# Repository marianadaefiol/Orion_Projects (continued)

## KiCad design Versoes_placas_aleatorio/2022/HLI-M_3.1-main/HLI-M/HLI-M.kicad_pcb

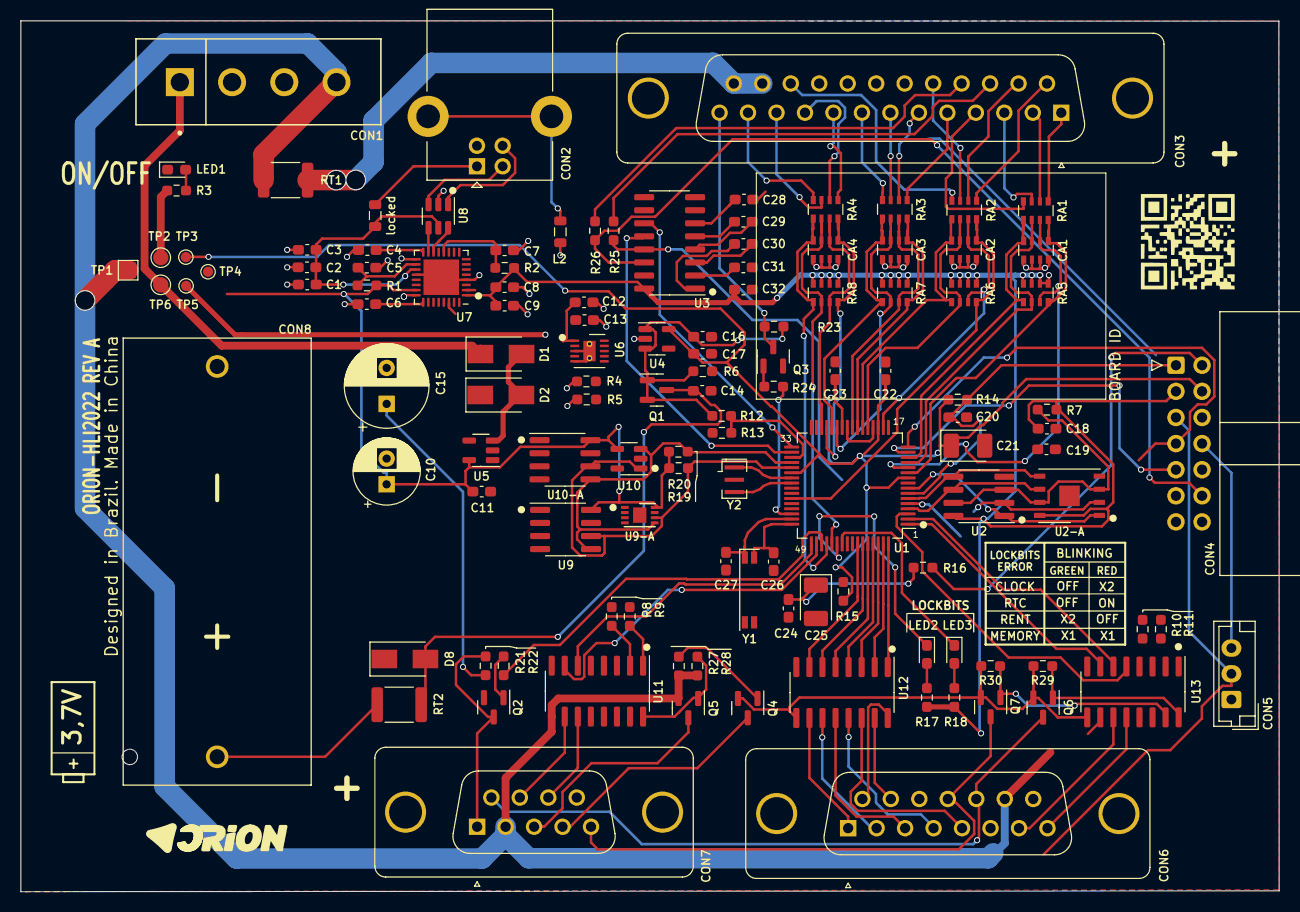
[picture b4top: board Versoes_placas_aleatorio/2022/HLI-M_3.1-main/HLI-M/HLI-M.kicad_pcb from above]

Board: 2 copper layers, 122.4 x 84.7 mm, 124 parts (0 on the bottom side), 132 nets.

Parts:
C1, C3, C5, C7, C9, C11, C14, C16, C17, C18, C22, C23, C24, C28, C29, C30, C31, C32: 100nF; C_0603_1608Metric_Pad1.08x0.95mm_HandSolder
C2, C8: 4,7uF; C_0603_1608Metric_Pad1.08x0.95mm_HandSolder
C4, C12, C13: 1uF; C_0603_1608Metric_Pad1.08x0.95mm_HandSolder
C6: 2,2nF; C_0603_1608Metric_Pad1.08x0.95mm_HandSolder
C10: 220uFx16V; CP_Radial_D6.3mm_P2.50mm
C15: 470uFx16v; CP_Radial_D8.0mm_P3.50mm
C19: 47pF; C_0603_1608Metric_Pad1.08x0.95mm_HandSolder
C20: 1nF; C_0603_1608Metric_Pad1.08x0.95mm_HandSolder
C21: 10UfX6V-Tan; CP_EIA-3528-12_Kemet-T_Pad1.50x2.35mm_HandSolder
C25: 10uFx6V-Tan; CP_EIA-3528-12_Kemet-T_Pad1.50x2.35mm_HandSolder
C26, C27: 12pF; C_0603_1608Metric_Pad1.08x0.95mm_HandSolder
CA1: 100nF; R_Array_Convex_4x0603
CA2, CA3, CA4: Array_Cap; R_Array_Convex_4x0603
CON1: Molex-0015244449-0
CON2: USB_B; USB_B_Lumberg_2411_02_Horizontal
CON3: DSUB-25_Male_Vertical_P2.77x2.84mm_MountingHoles
CON4: Connector_Adapter; IDC-Header_2x07_P2.54mm_Horizontal
CON5: Connector_Audio; JST_EH_B3B-EH-A_1x03_P2.50mm_Vertical
CON6: Conn_01x15; DSUB-15_Female_Vertical_P2.77x2.84mm_MountingHoles
CON7: Conn_01x09; DSUB-9_Female_Vertical_P2.77x2.84mm_MountingHoles
CON8: CR123A; BAT_BH123A
D1, D2: SSA33L; D_SMA
D8: SD1-13F; D_SMA
G1: LOGO
L2: BLM21PG221SN1D; L_0805_2012Metric
LED1: BLUE; LED_0603_1608Metric_Pad1.05x0.95mm_HandSolder
LED2: RED; LED_0603_1608Metric_Pad1.05x0.95mm_HandSolder
LED3: GREEN; LED_0603_1608Metric_Pad1.05x0.95mm_HandSolder
Q1: IRLML5103; SOT-23
Q2, Q3: BC817; SOT-23
Q4, Q5, Q6, Q7: BSS84; SOT-23
R1, R2: 2,2K; R_0603_1608Metric_Pad0.98x0.95mm_HandSolder
R3, R17, R18: 470R; R_0603_1608Metric_Pad0.98x0.95mm_HandSolder
R4, R5, R6: 10k; R_0603_1608Metric_Pad0.98x0.95mm_HandSolder
R7, R14: 22k; R_0603_1608Metric_Pad0.98x0.95mm_HandSolder
R8, R9, R10, R11, R16, R19, R20, R21, R23, R27, R28, R29, R30: 1K; R_0603_1608Metric_Pad0.98x0.95mm_HandSolder
R12: 1K5; R_0603_1608Metric_Pad0.98x0.95mm_HandSolder
R13: 3K3; R_0603_1608Metric_Pad0.98x0.95mm_HandSolder
R15, R22, R24: 22K; R_0603_1608Metric_Pad0.98x0.95mm_HandSolder
R25, R26: 33R; R_0603_1608Metric_Pad0.98x0.95mm_HandSolder
RA1: 1K; R_Array_Convex_4x0603
RA2, RA3, RA4, RA6, RA7, RA8: R_Pack04; R_Array_Convex_4x0603
RA5: 10K; R_Array_Convex_4x0603
RT1: 1,5A - 153F; R_1812_4532Metric
RT2: 300mA - 304N; R_1812_4532Metric
TP1: TestPoint; TestPoint_Pad_1.5x1.5mm
TP2, TP6: TestPoint; TestPoint_Pad_D1.5mm
TP3, TP4, TP5: TestPoint; TestPoint_Pad_D1.0mm
U1: PIC24HJ64GP206-I_PT; TQFP-64_10x10mm_P0.5mm
U2, U9, U10-A: SOIC-8_3.9x4.9mm_P1.27mm
U2-A: DFN-8-1EP_6x5mm_P1.27mm_EP2x2mm
U3: MAX3232; SOIC-16_3.9x9.9mm_P1.27mm
U4, U5: TPS7A0533PDBV; SOT-23-5
U6: VSON-10-1EP_3x3mm_P0.5mm_EP1.2x2mm_ThermalVias
U7: CY7C65215-32LTXI; QFN-32-1EP_5x5mm_P0.5mm_EP3.45x3.45mm
U8: USBLC6-2SC6; SOT-23-6
U9-A: DFN-8-1EP_3x2mm_P0.5mm_EP1.3x1.5mm
U10: 24AA02-OT; SOT-23-5
U11, U12, U13: ULN2003; SOIC-16_3.9x9.9mm_P1.27mm
Y1: Crystal_32KHz; Crystal_SMD_SeikoEpson_MC146-4Pin_6.7x1.5mm
Y2: Crystal_20MHz; Resonator_SMD_Murata_CSTxExxV-3Pin_3.0x1.1mm
locked: BLM21PG221SN1D; L_0805_2012Metric

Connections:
0: C1.2, C2.2, C3.2, C4.2, C5.2, C6.2, C7.2, C8.2, C9.2, C10.2, C11.2, C12.2, C13.2, C14.2, C15.2, C16.2, C17.2, C18.2, C19.2, C20.2, C21.2, C22.2, C23.2, C24.2, C25.2, C26.2, C27.2, C28.2, C31.2, C32.2, CA1.5, CA1.6, CA1.7, CA1.8, CA2.5, CA2.6, CA2.7, CA2.8, CA3.5, CA3.6, CA3.7, CA3.8, CA4.5, CA4.6, CA4.7, CA4.8, CON1.2, CON1.3, CON2.4 (GND), CON3.20, CON3.21, CON3.22, CON6.15, CON7.9, CON8.N, D8.1 (K), L2.1, LED1.1 (K), Q2.2 (E), Q3.2 (E), R4.1, R5.2, R6.2, R13.1, U1.9 (VSS), U1.20 (AVSS), U1.25 (VSS), U1.41 (VSS), U2.4 (VSS), U2-A.4, U3.15 (GND), U4.2 (GND), U5.2 (GND), U6.3 (GND), U6.5 (EN_B), U6.11 (DAP), U7.4 (VSSD), U7.17 (VSSD), U7.20 (VSSD), U7.24 (VSSA), U8.2 (GND), U9.4 (GND), U9-A.4, U10.2 (GND), U10-A.4, U11.8 (GND), U12.8 (GND), U13.8 (GND), Y1.2, Y2.2
+2V5: CON4.2, R16.1
+3.3VP: C17.1, C21.1, C22.1, C23.1, CON4.4, R14.1, R15.1, TP3.1, U1.10 (VDD), U1.19 (AVDD), U1.26 (VDD), U1.38 (VDD), U4.5 (OUT)
+5V: C12.1, CON1.1, CON3.19, CON4.6, CON5.1, D1.1 (K), TP6.1, U6.1 (CHG_IN)
+5VD: C15.1, C16.1, D1.2 (A), D2.2 (A), Q1.1 (G), Q1.2 (S), R3.1, R6.1, R12.2, R21.1, R23.1, TP2.1, U4.1 (IN), U4.3 (EN), U5.1 (IN), U5.3 (EN)
+12V: CON1.4, CON4.8, CON5.3, CON6.14, CON7.2, Q4.2 (S), Q5.2 (S), Q6.2 (S), Q7.2 (S), R27.1, R28.1, R29.1, R30.1, RT1.2, TP1.1, U11.9 (COM), U12.9 (COM), U13.9 (COM)
CIN: CON6.13, CON7.6, Q6.3 (D)
CIN1: CON7.3, Q5.3 (D)
COUT: CON6.12, CON7.5, Q7.3 (D)
COUT1: CON7.4, Q4.3 (D)
GND: CON4.5, CON5.2
INIB: CON3.13, Q3.3 (C), R23.2
K0: CA1.1, RA1.8 (R1.2), RA5.8 (R1.2), U1.11 (RB5)
K1: CA1.2, RA1.7 (R2.2), RA5.7 (R2.2), U1.12 (RB4)
K2: CA1.3, RA1.6 (R3.2), RA5.6 (R3.2), U1.13 (RB3)
K3: CA1.4, RA1.5 (R4.2), RA5.5 (R4.2), U1.14 (RB2)
K4: CA3.1, RA3.8 (R1.2), RA7.8 (R1.2), U1.23 (RB10)
K5: CA3.2, RA3.7 (R2.2), RA7.7 (R2.2), U1.24 (RB11)
K6: CA3.3, RA3.6 (R3.2), RA7.6 (R3.2), U1.27 (RB12)
K7: CA3.4, RA3.5 (R4.2), RA7.5 (R4.2), U1.28 (RB13)
K8: CA4.1, RA4.8 (R1.2), RA8.8 (R1.2), U1.29 (RB14)
K9: CA4.2, RA4.7 (R2.2), RA8.7 (R2.2), U1.30 (RB15)
KA: CA4.3, RA4.6 (R3.2), RA8.6 (R3.2), U1.53 (RD5)
KB: CA4.4, RA4.5 (R4.2), RA8.5 (R4.2), U1.52 (RD4)
KC: CA2.2, RA2.7 (R2.2), RA6.7 (R2.2), U1.18 (RB7)
KD: CA2.3, RA2.6 (R3.2), RA6.6 (R3.2), U1.21 (RB8)
KE: CA2.4, RA2.5 (R4.2), RA6.5 (R4.2), U1.22 (RB9)
K_0: CON3.1, RA1.1 (R1.1)
K_1: CON3.2, RA1.2 (R2.1)
K_2: CON3.3, RA1.3 (R3.1)
K_3: CON3.4, RA1.4 (R4.1)
K_4: CON3.5, RA3.1 (R1.1)
K_5: CON3.6, RA3.2 (R2.1)
K_6: CON3.7, RA3.3 (R3.1)
K_7: CON3.8, RA3.4 (R4.1)
K_8: CON3.9, RA4.1 (R1.1)
K_9: CON3.10, RA4.2 (R2.1)
K_A: CON3.11, RA4.3 (R3.1)
K_B: CON3.12, RA4.4 (R4.1)
K_C: CON3.15, RA2.2 (R2.1)
K_D: CON3.18, RA2.3 (R3.1)
K_E: CON3.23, RA2.4 (R4.1)
LED2: LED2.1 (K), U1.54 (RD6)
LED3: LED3.1 (K), U1.55 (RD7)
NOTE: CA2.1, RA2.8 (R1.2), RA6.8 (R1.2), U1.43 (RD9)
NOTE_: CON3.14, RA2.1 (R1.1)
unnamed: C1.1, C2.1, C3.1, D2.1 (K), U7.19 (VBUS), U8.5 (VBUS), locked.2
unnamed: C4.1, U7.16 (VCCD)
unnamed: C5.1, R1.2, U7.18 (~XRES)
unnamed: C6.1, U7.25 (GPIO_0)
unnamed: C7.1, R2.2, U7.12 (WAKEUP)
unnamed: U1.4 (SCK2/RG6), U2.6 (C), U2-A.6
unnamed: C24.1, C25.1, R16.2
unnamed: C26.1, U1.48 (RC14), Y1.3
unnamed: C27.1, Y1.1
unnamed: C28.1, U3.6 (VS-)
unnamed: C29.1, U3.4 (C2+)
unnamed: C29.2, U3.5 (C2-)
unnamed: C30.1, U3.1 (C1+)
unnamed: C30.2, U3.3 (C1-)
unnamed: C31.1, U3.2 (VS+)
unnamed: CON2.1 (VBUS), locked.1
unnamed: CON2.2 (D-), U8.3 (I/O2)
unnamed: CON2.3 (D+), U8.1 (I/O1)
unnamed: CON2.5 (Shield), L2.2
unnamed: CON3.16, R25.2
unnamed: CON3.17, R26.2
unnamed: CON3.24, CON3.25, RT1.1
unnamed: CON6.1, U12.10 (O7)
unnamed: CON6.2, U12.11 (O6)
unnamed: CON6.3, U12.12 (O5)
unnamed: CON6.4, U12.13 (O4)
unnamed: CON6.5, U12.14 (O3)
unnamed: CON6.6, U13.10 (O7)
unnamed: CON6.7, U13.11 (O6)
unnamed: CON6.8, U13.12 (O5)
unnamed: CON6.9, U12.16 (O1)
unnamed: CON6.10, U12.15 (O2)
unnamed: CON7.7, U11.10 (O7)
unnamed: CON7.8, U11.11 (O6)
unnamed: CON8.P, RT2.1
unnamed: LED1.2 (A), R3.2
unnamed: LED2.2 (A), R17.2
unnamed: LED3.2 (A), R18.2
unnamed: Q2.1 (B), R22.1
unnamed: Q3.1 (B), R24.1
unnamed: Q4.1 (G), R27.2, U11.15 (O2)
unnamed: Q5.1 (G), R28.2, U11.16 (O1)
unnamed: Q6.1 (G), R29.2, U13.16 (O1)
unnamed: Q7.1 (G), R30.2, U13.15 (O2)
unnamed: U2.3 (*W), U2.7 (*HOLD), U2-A.3, U2-A.7
unnamed: U1.5 (SDI2/RG7), U2.2 (Q), U2-A.2
unnamed: U1.6 (SDO2/RG8), U2.5 (D), U2-A.5
unnamed: U1.8 (*SS2/RG9), U2.1 (*S), U2-A.1
unnamed: U1.33 (U1TX/RF3), U3.11 (T1IN)
unnamed: U1.34 (U1RX/RF2), U3.12 (R1OUT)
unnamed: U1.39 (OSC1/CLKIN), Y2.1
unnamed: U1.40 (OSC2/CLKO), Y2.3
unnamed: C13.1, U6.4 (USB_SEL)
unnamed: U7.14 (USBDP), U8.6 (I/O1)
unnamed: U7.15 (USBDM), U8.4 (I/O2)
PGEC2: CON4.9, R11.1, U1.15 (RB1)
PGED2: CON4.7, R10.1, U1.16 (RB0)
PIN-CIN: R10.2, U13.2 (I2)
PIN-CIN1: R8.2, U11.2 (I2)
PIN-COUT: R11.2, U13.1 (I1)
PIN-COUT1: R9.2, U11.1 (I1)
PIN-INIB: R24.2, U1.46 (RD0)
PIN-PRINT: R22.2, U1.51 (RD3)
PIN-PWRMODE: R12.1, R13.2, U1.35 (RF6)
PIN-S0: U1.58 (RF0), U12.7 (I7)
PIN-S1: U1.59 (RF1), U12.6 (I6)
PIN-S2: U1.60 (RG1), U12.5 (I5)
PIN-S3: U1.61 (RG0), U12.4 (I4)
PIN-S4: U1.62 (RG14), U12.3 (I3)
PIN-S5: U1.1 (RG15), U13.7 (I7)
PIN-S6: U1.2 (RC1), U13.6 (I6)
PIN-S7: U1.3 (RC2), U13.5 (I5)
PIN-S8: U1.64 (RG13), U12.1 (I1)
PIN-S9: U1.63 (RG12), U12.2 (I2)
PIN-S10: U1.50 (RD2), U11.7 (I7)
PIN-S11: U1.49 (RD1), U11.6 (I6)
PIN-SCL: R19.2, U1.37 (SCL1/RG2), U9.6 (SCL), U9-A.6, U10.1 (SCL), U10-A.6
PIN-SDA: R20.2, U1.36 (SDA1/RG3), U9.5 (SDA), U9-A.5, U10.3 (SDA), U10-A.5
PRINT_IMP: CON7.1, Q2.3 (C), R21.2
RESET: C20.1, CON4.1, R14.2, U1.7 (*MCLR)
RXA: U1.32 (U2TX/RF5), U7.2 (SCB0_0/GPIO_8)
RXP: CON4.14, R25.1, U3.13 (R1IN)
TXA: U1.31 (U2RX/RF4), U7.30 (SCB0_4/GPIO_5)
TXP: CON4.12, R26.1, U3.14 (T1OUT)
VBAT: C14.1, CON4.10, D8.2 (A), Q1.3 (D), RT2.2, TP5.1
VDDD: C8.1, C9.1, C10.1, C11.1, C18.1, C32.1, CON4.3, R1.1, R2.1, R7.1, R17.1, R18.1, R19.1, R20.1, RA5.1 (R1.1), RA5.2 (R2.1), RA5.3 (R3.1), RA5.4 (R4.1), RA6.1 (R1.1), RA6.2 (R2.1), RA6.3 (R3.1), RA6.4 (R4.1), RA7.1 (R1.1), RA7.2 (R2.1), RA7.3 (R3.1), RA7.4 (R4.1), RA8.1 (R1.1), RA8.2 (R2.1), RA8.3 (R3.1), RA8.4 (R4.1), TP4.1, U2.8 (VDD), U2-A.8, U3.16 (VCC), U5.5 (OUT), U7.1 (VDDD), U7.23 (VDDD), U9.8 (VCC), U9-A.8, U10.4 (VCC), U10-A.8

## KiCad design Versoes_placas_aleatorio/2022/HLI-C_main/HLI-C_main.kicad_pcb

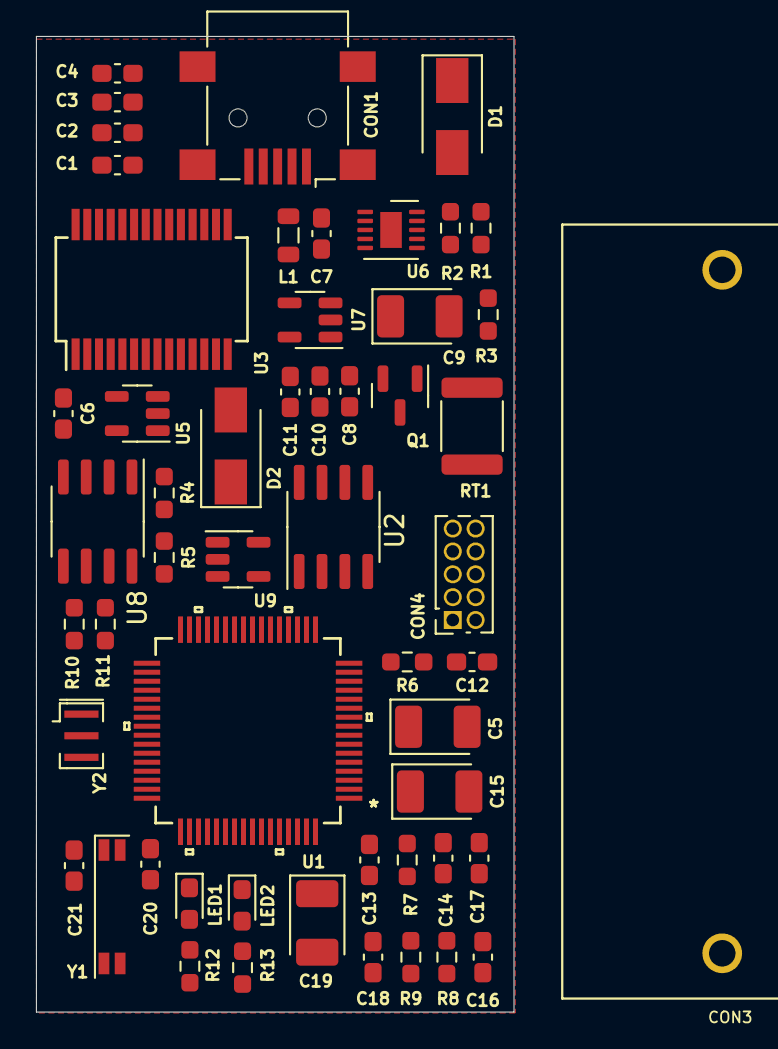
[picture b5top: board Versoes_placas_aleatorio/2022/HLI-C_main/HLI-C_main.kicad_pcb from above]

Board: 2 copper layers, 26.5 x 54.2 mm, 54 parts (0 on the bottom side), 38 nets, no tracks yet.

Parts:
C1, C6, C8, C10, C11, C12, C16, C17, C18: 100nF; C_0603_1608Metric_Pad1.08x0.95mm_HandSolder
C2: 10nF; C_0603_1608Metric_Pad1.08x0.95mm_HandSolder
C3: 4,7uF; C_0603_1608Metric_Pad1.08x0.95mm_HandSolder
C4, C7: 1uF; C_0603_1608Metric_Pad1.08x0.95mm_HandSolder
C5: 220uFx16V; CP_EIA-3528-12_Kemet-T_Pad1.50x2.35mm_HandSolder
C9: 470uFx16v; CP_EIA-3528-12_Kemet-T_Pad1.50x2.35mm_HandSolder
C13: 47pF; C_0603_1608Metric_Pad1.08x0.95mm_HandSolder
C14: 1nF; C_0603_1608Metric_Pad1.08x0.95mm_HandSolder
C15: 10UfX6V-Tan; CP_EIA-3528-12_Kemet-T_Pad1.50x2.35mm_HandSolder
C19: 10uFx6V-Tan; CP_EIA-3528-12_Kemet-T_Pad1.50x2.35mm_HandSolder
C20, C21: 12pF; C_0603_1608Metric_Pad1.08x0.95mm_HandSolder
CON1: USB_B; USB_Mini-B_Lumberg_2486_01_Horizontal
CON3: CR123A; BAT_BH123A
CON4: Conn_02x05_Odd_Even; PinSocket_2x05_P1.27mm_Vertical
D1, D2: SSA33L; D_SMA
L1: BLM21PG221SN1D; L_0805_2012Metric
LED1: RED; LED_0603_1608Metric_Pad1.05x0.95mm_HandSolder
LED2: GREEN; LED_0603_1608Metric_Pad1.05x0.95mm_HandSolder
Q1: IRLML5103; SOT-23
R1, R2, R3: 10k; R_0603_1608Metric_Pad0.98x0.95mm_HandSolder
R4, R5, R9: 1K; R_0603_1608Metric_Pad0.98x0.95mm_HandSolder
R6, R7: 22k; R_0603_1608Metric_Pad0.98x0.95mm_HandSolder
R8: 22K; R_0603_1608Metric_Pad0.98x0.95mm_HandSolder
R10: 1K5; R_0603_1608Metric_Pad0.98x0.95mm_HandSolder
R11: 3K3; R_0603_1608Metric_Pad0.98x0.95mm_HandSolder
R12, R13: 470R; R_0603_1608Metric_Pad0.98x0.95mm_HandSolder
RT1: 300mA - 304N; R_1812_4532Metric
U1: PIC24HJ64GP206-I_PT; PIC24HJ64GP206-I_slash_PT
U2: FM25V10-GTR; SOIC-8_3.9x4.9mm_P1.27mm
U3: FT232RL; SSOP-28_5.3x10.2mm_P0.65mm
U5, U7: TPS7A0533PDBV; SOT-23-5
U6: LM3658SD; VSON-10-1EP_3x3mm_P0.5mm_EP1.2x2mm
U8: ATSHA204A-SSHDA-B; SOIC-8_3.9x4.9mm_P1.27mm
U9: 24AA02-OT; SOT-23-5
Y1: Crystal_32KHz; Crystal_SMD_SeikoEpson_MC146-4Pin_6.7x1.5mm
Y2: Crystal_20MHz; Resonator_SMD_Murata_CSTxExxV-3Pin_3.0x1.1mm

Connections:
0: C1.2, C2.2, C3.2, C4.2, C5.2, C6.2, C7.2, C8.2, C9.2, C10.2, C11.2, C12.2, C13.2, C14.2, C15.2, C16.2, C17.2, C18.2, C19.2, C20.2, C21.2, CON1.4 (GND), D1.1 (K), L1.1, R1.2, R2.1, R3.2, R11.1, U1.9 (VSS), U1.20 (AVSS), U1.25 (VSS), U1.41 (VSS), U2.4 (VSS), U3.7 (GND), U3.18 (GND), U3.21 (GND), U3.25 (AGND), U3.26 (TEST), U5.2 (GND), U6.3 (GND), U6.5 (EN_B), U7.2 (GND), U8.4 (GND), U9.2 (GND), Y1.2, Y2.2
+2V5: CON4.2, R9.1
+3.3VP: C11.1, C15.1, C16.1, C17.1, CON4.4, R7.1, R8.1, U1.10 (VDD), U1.19 (AVDD), U1.26 (VDD), U1.38 (VDD), U7.5 (OUT)
+3V3: C5.1, C6.1, C12.1, CON4.3, R4.1, R5.1, R6.1, R12.1, R13.1, U2.8 (VDD), U5.5 (OUT), U8.8 (VCC), U9.4 (VCC)
+5VD: C9.1, C10.1, Q1.1 (G), Q1.2 (S), R3.1, R10.2, U7.1 (IN), U7.3 (EN)
LED2: LED1.1 (K), U1.54 (RD6)
LED3: LED2.1 (K), U1.55 (RD7)
unnamed: C4.1, U3.4 (VCCIO), U3.17 (3V3OUT)
unnamed: C7.1, U6.4 (USB_SEL)
unnamed: C8.1, D1.2 (A), Q1.3 (D), RT1.2, U6.10 (BATT)
unnamed: C13.1, U1.4 (SCK2/RG6), U2.6 (C)
unnamed: C18.1, C19.1, R9.2, U1.56 (VDDCORE)
unnamed: C20.1, U1.48 (RC14), Y1.3
unnamed: C21.1, U1.47 (RC13), Y1.1
unnamed: CON1.2 (D-), U3.16 (USBD-)
unnamed: CON1.3 (D+), U3.15 (USBD+)
unnamed: CON1.5 (Shield), L1.2
unnamed: C1.1, C2.1, C3.1, CON1.1 (VBUS), D2.1 (K), U3.20 (VCC), U6.2 (USBPWR)
unnamed: D2.2 (A), U5.1 (IN), U5.3 (EN)
unnamed: LED1.2 (A), R12.2
unnamed: LED2.2 (A), R13.2
unnamed: R1.1, U6.9 (TS)
unnamed: R2.2, U6.8 (ISET)
unnamed: R6.2, U2.3 (*W), U2.7 (*HOLD)
unnamed: R8.2, U1.57 (VDD)
unnamed: U1.5 (SDI2/RG7), U2.2 (Q)
unnamed: U1.6 (SDO2/RG8), U2.5 (D)
unnamed: U1.8 (*SS2/RG9), U2.1 (*S)
unnamed: U1.39 (OSC1/CLKIN), Y2.1
unnamed: U1.40 (OSC2/CLKO), Y2.3
PGEC2: CON4.9, U1.15 (RB1)
PGED2: CON4.7, U1.16 (RB0)
PIN-PWRMODE: R10.1, R11.2, U1.35 (RF6)
PIN-SCL: R4.2, U1.37 (SCL1/RG2), U8.6 (SCL), U9.1 (SCL)
PIN-SDA: R5.2, U1.36 (SDA1/RG3), U8.5 (SDA), U9.3 (SDA)
RESET: C14.1, CON4.1, R7.2, U1.7 (*MCLR)
RXA: CON4.8, U1.32 (U2TX/RF5), U3.5 (RXD)
TXA: CON4.10, U1.31 (U2RX/RF4), U3.1 (TXD)

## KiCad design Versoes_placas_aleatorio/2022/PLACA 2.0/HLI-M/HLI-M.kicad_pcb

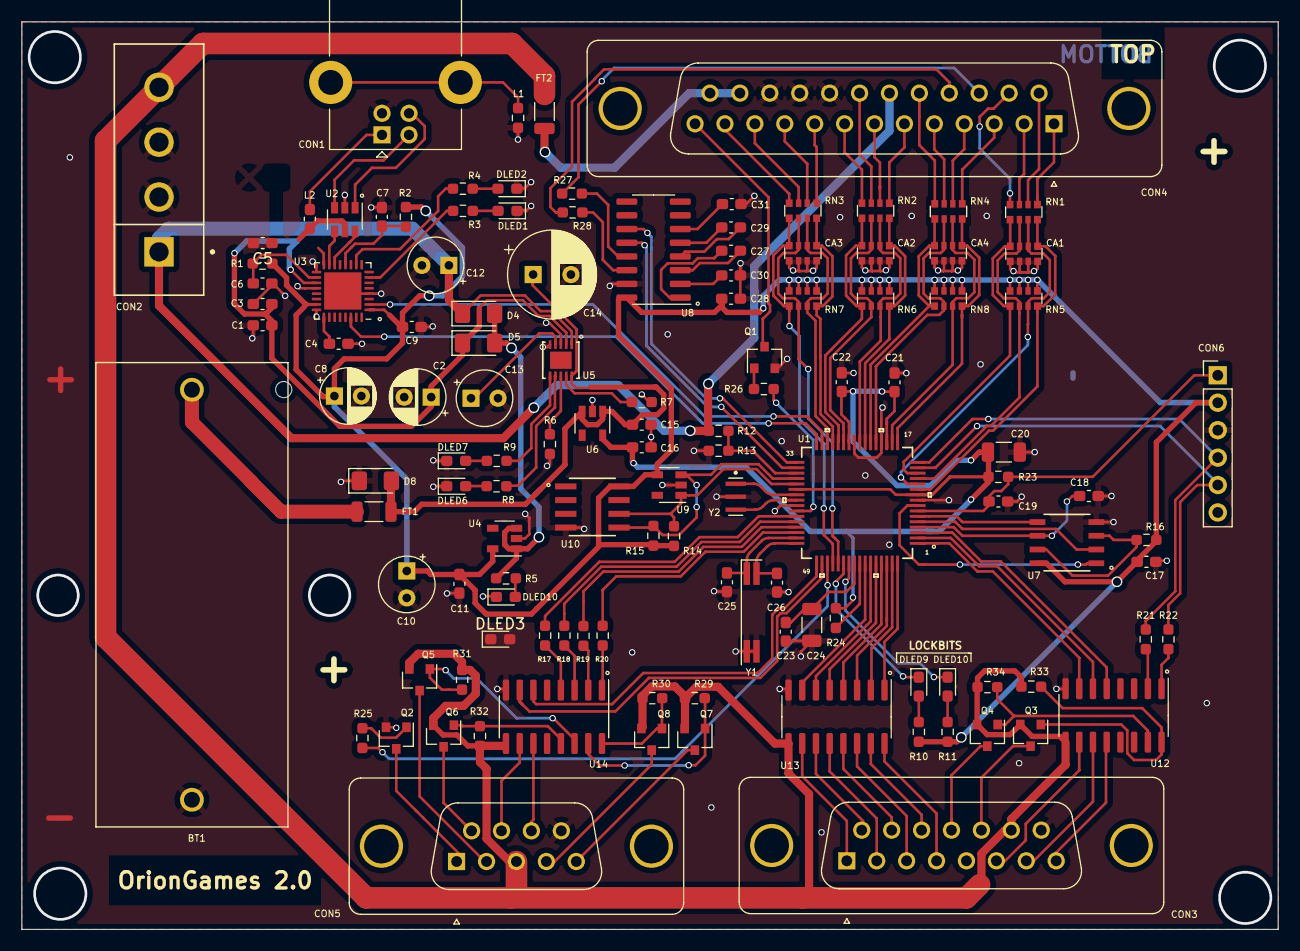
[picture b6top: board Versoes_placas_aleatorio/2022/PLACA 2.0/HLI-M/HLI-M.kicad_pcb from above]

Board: 2 copper layers, 116.3 x 84.0 mm, 122 parts (0 on the bottom side), 151 nets.

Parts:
BT1: Battery; BAT_BH123A
C1, C6, C7, C11, C15, C16, C17, C21, C22, C23, C27, C28, C29, C30, C31: 100nF; C_0603_1608Metric_Pad1.08x0.95mm_HandSolder
C2, C8: 4,7uF; CP_Radial_D5.0mm_P2.50mm
C3, C9: 0,1uF; C_0603_1608Metric_Pad1.08x0.95mm_HandSolder
C4: 2,2nF; C_0603_1608Metric_Pad1.08x0.95mm_HandSolder
C5: 1uF; C_0603_1608Metric_Pad1.08x0.95mm_HandSolder
C10: 220uFx16V; CP_Radial_Tantal_D5.0mm_P2.50mm
C12, C13: 1uF; CP_Radial_Tantal_D5.0mm_P2.50mm
C14: 470uFx16v; CP_Radial_D8.0mm_P3.50mm
C18: 47pF; C_0603_1608Metric_Pad1.08x0.95mm_HandSolder
C19: 1nF; C_0603_1608Metric_Pad1.08x0.95mm_HandSolder
C20: 10UfX6V-Tan; C_1206_3216Metric
C24: 10uFx6V-Tan; C_1206_3216Metric
C25, C26: 12pF; C_0603_1608Metric_Pad1.08x0.95mm_HandSolder
CA1: 100nF; R_Array_Convex_4x0612
CA2, CA3, CA4: Array_Cap; R_Array_Convex_4x0612
CON1: USB_B; USB_B_Lumberg_2411_02_Horizontal
CON2: Molex-0015244449-0
CON3: Conn_01x15; DSUB-15_Female_Vertical_P2.77x2.84mm_MountingHoles
CON4: DSUB-25_Male_Vertical_P2.77x2.84mm_MountingHoles
CON5: Conn_01x09; DSUB-9_Female_Vertical_P2.77x2.84mm_MountingHoles
CON6: Conn_01x06; PinHeader_1x06_P2.54mm_Vertical
D4, D5, D8: DIODE; D_1206_3216Metric_Pad1.42x1.75mm_HandSolder
DLED1, DLED2, DLED9: RED; LED_0603_1608Metric_Pad1.05x0.95mm_HandSolder
DLED3: BLUE; LED_0603_1608Metric_Pad1.05x0.95mm_HandSolder
DLED6, DLED7, DLED10, DLED10#2: GREEN; LED_0603_1608Metric_Pad1.05x0.95mm_HandSolder
FT1, FT2: Fusistor; L_1206_3216Metric
L1: INDUCTOR; R_0603_1608Metric_Pad0.98x0.95mm_HandSolder
L2: INDUCTOR; L_0603_1608Metric_Pad1.05x0.95mm_HandSolder
Q1, Q2: BC817; SOT-23
Q3, Q4, Q5, Q6, Q7, Q8: BSS84; SOT-23
R1, R2: 2,2K; R_0603_1608Metric_Pad0.98x0.95mm_HandSolder
R3, R4, R5, R10, R11: 470R; R_0603_1608Metric_Pad0.98x0.95mm_HandSolder
R6, R7: 10k; R_0603_1608Metric_Pad0.98x0.95mm_HandSolder
R8, R9: 470; R_0603_1608Metric_Pad0.98x0.95mm_HandSolder
R12: 1K8; R_0603_1608Metric_Pad0.98x0.95mm_HandSolder
R13: 3K3; R_0603_1608Metric_Pad0.98x0.95mm_HandSolder
R14, R15, R29, R30, R31, R32, R33, R34: 1K; R_0603_1608Metric_Pad0.98x0.95mm_HandSolder
R16, R23, R24: 22k; R_0603_1608Metric_Pad0.98x0.95mm_HandSolder
R17, R18, R19, R20, R21, R22: 22K; R_0603_1608Metric_Pad0.98x0.95mm_HandSolder
R25, R26: 10K; R_0603_1608Metric_Pad0.98x0.95mm_HandSolder
R27, R28: 33R; R_0603_1608Metric_Pad0.98x0.95mm_HandSolder
RN1: 1K; R_Array_Convex_4x0612
RN2, RN3, RN4, RN6, RN7, RN8: R_Pack04; R_Array_Convex_4x0612
RN5: 12K; R_Array_Convex_4x0612
U1: PIC24HJ64GP206-I_PT; PIC24HJ64GP206-I&slash_PT
U2: USBLC6-2SC6; SOT-23-6
U3: CY7C65215-32LTXI; QFN-32-1EP_5x5mm_P0.5mm_EP3.45x3.45mm
U4, U6: TPS7A0533PDBV; SOT-23-5
U5: LM3658SD
U7: FM25V10-GTR
U8: MAX3232; SOIC-16_3.9x9.9mm_P1.27mm
U9: 24AA02-OT; SOT-23-5
U10: ATSHA204A-SSHDA-B
U12, U13, U14: ULN2003; SOIC-16_3.9x9.9mm_P1.27mm
Y1: Crystal_GND2_Small; Crystal_SMD_SeikoEpson_MC146-4Pin_6.7x1.5mm_HandSoldering
Y2: Crystal_GND2_Small; OSC_CSTNE20M0VH3C000R0

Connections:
0: C1.2, C2.2, C3.2, C4.2, C5.2, C6.2, C7.2, C8.2, C9.2, C10.2, C11.2, C12.2, C13.2, C14.2, C15.2, C16.2, C17.2, C18.2, C19.2, C20.2, C21.2, C22.2, C23.2, C24.2, C25.2, C26.2, C28.2, C30.2, C31.2, CA1.5, CA1.6, CA1.7, CA1.8, CA2.5, CA2.6, CA2.7, CA2.8, CA3.5, CA3.6, CA3.7, CA3.8, CA4.5, CA4.6, CA4.7, CA4.8, CON1.4 (GND), CON2.2, CON2.3, CON3.15, CON4.21, CON4.22, CON4.23, D8.1 (K), DLED1.1 (K), DLED2.1 (K), DLED3.1 (K), DLED6.1 (K), DLED7.1 (K), L1.1, Q1.2 (E), Q2.2 (E), R6.1, R7.2, R13.1, U1.9 (VSS), U1.20 (AVSS), U1.25 (VSS), U1.41 (VSS), U2.2 (GND), U3.4 (VSSD), U3.17 (VSSD), U3.20 (VSSD), U3.24 (VSSA), U4.2 (GND), U5.3 (GND), U5.5 (EN_B), U6.2 (GND), U7.4 (VSS), U8.15 (GND), U9.2 (GND), U10.4 (GND), U12.8 (GND), U13.8 (GND), U14.8 (GND), Y1.2, Y2.2
+3.3VP: C16.1, C20.1, C21.1, C22.1, R23.1, R24.2, U1.10 (VDD), U1.19 (AVDD), U1.26 (VDD), U1.38 (VDD), U6.5 (OUT)
+5V: C12.1, CON2.1, CON4.19, D4.1 (K), R12.2, U5.1 (CHG_IN)
+12V: CON2.4, CON3.14, CON5.3, FT2.1, Q3.2 (S), Q4.2 (S), Q5.2 (S), Q6.2 (S), Q7.2 (S), Q8.2 (S), R29.1, R30.1, R31.1, R32.1, R33.1, R34.1, U12.9 (COM), U13.9 (COM), U14.9 (COM)
CIN: CON3.13, Q3.3 (D)
CIN1: CON5.4, Q8.3 (D)
CIN2: CON5.2, Q5.3 (D)
COUT: CON3.12, Q4.3 (D)
COUT1: CON5.5, Q7.3 (D)
COUT2: CON5.6, Q6.3 (D)
GND: CON5.9, CON6.3
INIB: CON4.13, Q1.3 (C)
K0: CA1.1, RN1.8 (R1.2), RN5.8 (R1.2), U1.11 (RB5)
K1: CA1.2, RN1.7 (R2.2), RN5.7 (R2.2), U1.12 (RB4)
K2: CA1.3, RN1.6 (R3.2), RN5.6 (R3.2), U1.13 (RB3)
K3: CA1.4, RN1.5 (R4.2), RN5.5 (R4.2), U1.14 (RB2)
K4: CA2.1, RN2.8 (R1.2), RN6.8 (R1.2), U1.23 (RB10)
K5: CA2.2, RN2.7 (R2.2), RN6.7 (R2.2), U1.24 (RB11)
K6: CA2.3, RN2.6 (R3.2), RN6.6 (R3.2), U1.27 (RB12)
K7: CA2.4, RN2.5 (R4.2), RN6.5 (R4.2), U1.28 (RB13)
K8: CA3.1, RN3.8 (R1.2), RN7.8 (R1.2), U1.29 (RB14)
K9: CA3.2, RN3.7 (R2.2), RN7.7 (R2.2), U1.30 (RB15)
KA: CA3.3, RN3.6 (R3.2), RN7.6 (R3.2), U1.53 (RD5)
KB: CA3.4, RN3.5 (R4.2), RN7.5 (R4.2), U1.52 (RD4)
KC: CA4.2, RN4.7 (R2.2), RN8.7 (R2.2), U1.18 (RB7)
KD: CA4.3, RN4.6 (R3.2), RN8.6 (R3.2), U1.21 (RB8)
KE: CA4.4, RN4.5 (R4.2), RN8.5 (R4.2), U1.22 (RB9)
K_0: CON4.1, RN1.1 (R1.1)
K_1: CON4.14, RN1.2 (R2.1)
K_2: CON4.2, RN1.3 (R3.1)
K_3: CON4.15, RN1.4 (R4.1)
K_4: CON4.6, RN2.1 (R1.1)
K_5: CON4.7, RN2.2 (R2.1)
K_6: CON4.20, RN2.3 (R3.1)
K_7: CON4.8, RN2.4 (R4.1)
K_8: CON4.9, RN3.1 (R1.1)
K_9: CON4.10, RN3.2 (R2.1)
K_A: CON4.11, RN3.3 (R3.1)
K_B: CON4.12, RN3.4 (R4.1)
K_C: CON4.4, RN4.2 (R2.1)
K_D: CON4.5, RN4.3 (R3.1)
K_E: CON4.18, RN4.4 (R4.1)
LED2: DLED9.1 (K), U1.54 (RD6)
LED3: DLED10.1 (K), DLED10#2.1 (K), U1.55 (RD7)
NOTE: CA4.1, RN4.8 (R1.2), RN8.8 (R1.2), U1.17 (RB6)
NOTE_: CON4.3, RN4.1 (R1.1)
unnamed: C1.1, C2.1, C3.1, D5.1 (K), L2.2, U2.5 (VBUS), U3.19 (VBUS), U5.2 (USBPWR)
unnamed: C4.1, U3.25 (GPIO_0)
unnamed: C5.1, U3.16 (VCCD)
unnamed: C6.1, R1.2, U3.18 (~XRES)
unnamed: C7.1, R2.2, U3.12 (WAKEUP)
unnamed: C13.1, U5.4 (USB_SEL)
unnamed: C14.1, C15.1, D8.2 (A), FT1.1, U5.10 (BATT), U6.1 (IN), U6.3 (EN)
unnamed: C18.1, U1.4 (SCK2/RG6), U7.6 (C)
unnamed: C23.1, C24.1, U1.56 (VDDCORE)
unnamed: C25.1, U1.47 (RC13), Y1.1
unnamed: C26.1, U1.48 (RC14), Y1.3
unnamed: C27.1, U8.1 (C1+)
unnamed: C27.2, U8.3 (C1-)
unnamed: C29.1, U8.4 (C2+)
unnamed: C29.2, U8.5 (C2-)
unnamed: C30.1, U8.2 (VS+)
unnamed: C31.1, U8.6 (VS-)
unnamed: CON1.1 (VBUS), L2.1
unnamed: CON1.2 (D-), U2.3 (I/O2)
unnamed: CON1.3 (D+), U2.1 (I/O1)
unnamed: CON1.5 (Shield), L1.2
unnamed: CON3.1, U13.10 (O7)
unnamed: CON3.2, U13.12 (O5)
unnamed: CON3.3, U13.14 (O3)
unnamed: CON3.4, U13.16 (O1)
unnamed: CON3.6, U12.10 (O7)
unnamed: CON3.7, U12.11 (O6)
unnamed: CON3.8, U12.12 (O5)
unnamed: CON3.9, U13.11 (O6)
unnamed: CON3.10, U13.13 (O4)
unnamed: CON3.11, U13.15 (O2)
unnamed: CON4.16, R27.1
unnamed: CON4.17, R28.1
unnamed: CON4.24, CON4.25, FT2.2
unnamed: CON5.7, U14.10 (O7)
unnamed: CON5.8, U14.11 (O6)
unnamed: D4.2 (A), D5.2 (A), R5.1, U4.1 (IN), U4.3 (EN)
unnamed: DLED1.2 (A), R3.1
unnamed: DLED2.2 (A), R4.1
unnamed: DLED3.2 (A), R5.2
unnamed: DLED6.2 (A), R8.1
unnamed: DLED7.2 (A), R9.2
unnamed: DLED9.2 (A), R10.2
unnamed: DLED10.2 (A), DLED10#2.2 (A), R11.2
unnamed: Q1.1 (B), R26.1
unnamed: Q2.1 (B), R25.1
unnamed: Q3.1 (G), R33.2, U12.16 (O1)
unnamed: Q4.1 (G), R34.2, U12.15 (O2)
unnamed: Q5.1 (G), R31.2, U14.14 (O3)
unnamed: Q6.1 (G), R32.2, U14.13 (O4)
unnamed: Q7.1 (G), R29.2, U14.15 (O2)
unnamed: Q8.1 (G), R30.2, U14.16 (O1)
unnamed: R3.2, U3.7 (SCB1_2/GPIO12)
unnamed: R4.2, U3.10 (SCB1_5/GPIO_15)
unnamed: R6.2, U5.8 (ISET)
unnamed: R7.1, U5.9 (TS)
unnamed: R8.2, U5.7 (STAT1)
unnamed: R9.1, U5.6 (STAT2)
unnamed: R16.2, U7.3 (*W), U7.7 (*HOLD)
unnamed: R17.1, U1.43 (RD9)
unnamed: R18.1, U1.44 (RD10)
unnamed: R19.1, U1.45 (RD11)
unnamed: R20.1, U1.46 (RD0)
unnamed: R24.1, U1.57 (VDD)
unnamed: U1.5 (SDI2/RG7), U7.2 (Q)
unnamed: U1.6 (SDO2/RG8), U7.5 (D)
unnamed: U1.8 (*SS2/RG9), U7.1 (*S)
unnamed: U1.33 (U1TX/RF3), U8.11 (T1IN)
unnamed: U1.34 (U1RX/RF2), U8.12 (R1OUT)
unnamed: U1.39 (OSC1/CLKIN), Y2.1
unnamed: U1.40 (OSC2/CLKO), Y2.3
unnamed: U2.4 (I/O2), U3.15 (USBDM)
unnamed: U2.6 (I/O1), U3.14 (USBDP)
PGEC2: CON6.5, R22.1, U1.15 (RB1)
PGED2: CON6.4, R21.1, U1.16 (RB0)
PIN-CIN: R21.2, U12.2 (I2)
PIN-CIN1: R17.2, U14.4 (I4)
PIN-CIN2: R19.2, U14.2 (I2)
PIN-COUT: R22.2, U12.1 (I1)
PIN-COUT1: R18.2, U14.3 (I3)
PIN-COUT2: R20.2, U14.1 (I1)
PIN-INIB: R26.2, U1.42 (RD8)
PIN-PRINT: R25.2, U1.51 (RD3)
PIN-PWRMODE: R12.1, R13.2, U1.35 (RF6)
PIN-S0: U1.58 (RF0), U13.7 (I7)
PIN-S1: U1.59 (RF1), U13.6 (I6)
PIN-S2: U1.60 (RG1), U13.5 (I5)
PIN-S3: U1.61 (RG0), U13.4 (I4)
PIN-S4: U1.62 (RG14), U13.3 (I3)
PIN-S5: U1.1 (RG15), U12.7 (I7)
PIN-S6: U1.2 (RC1), U12.6 (I6)
PIN-S7: U1.3 (RC2), U12.5 (I5)
PIN-S8: U1.64 (RG13), U13.1 (I1)
PIN-S9: U1.63 (RG12), U13.2 (I2)
PIN-S10: U1.50 (RD2), U14.7 (I7)
PIN-S11: U1.49 (RD1), U14.6 (I6)
PIN-SCL: R14.2, U1.37 (SCL1/RG2), U9.1 (SCL), U10.6 (SCL)
PIN-SDA: R15.2, U1.36 (SDA1/RG3), U9.3 (SDA), U10.5 (SDA)
PRINT_IMP: CON5.1, Q2.3 (C)
RESET: C19.1, CON6.1, R23.2, U1.7 (*MCLR)
RXA: U1.31 (U2RX/RF4), U3.2 (SCB0_0/GPIO_8)
RXP_: R27.2, U8.13 (R1IN)
TXA: U1.32 (U2TX/RF5), U3.30 (SCB0_4/GPIO_5)
TXP_: R28.2, U8.14 (T1OUT)
VDDD: C8.1, C9.1, C10.1, C11.1, C17.1, C28.1, CON6.2, R1.1, R2.1, R10.1, R11.1, R14.1, R15.1, R16.1, RN5.1 (R1.1), RN5.2 (R2.1), RN5.3 (R3.1), RN5.4 (R4.1), RN6.1 (R1.1), RN6.2 (R2.1), RN6.3 (R3.1), RN6.4 (R4.1), RN7.1 (R1.1), RN7.2 (R2.1), RN7.3 (R3.1), RN7.4 (R4.1), RN8.1 (R1.1), RN8.2 (R2.1), RN8.3 (R3.1), RN8.4 (R4.1), U3.1 (VDDD), U3.23 (VDDD), U4.5 (OUT), U7.8 (VDD), U8.16 (VCC), U9.4 (VCC), U10.8 (VCC)

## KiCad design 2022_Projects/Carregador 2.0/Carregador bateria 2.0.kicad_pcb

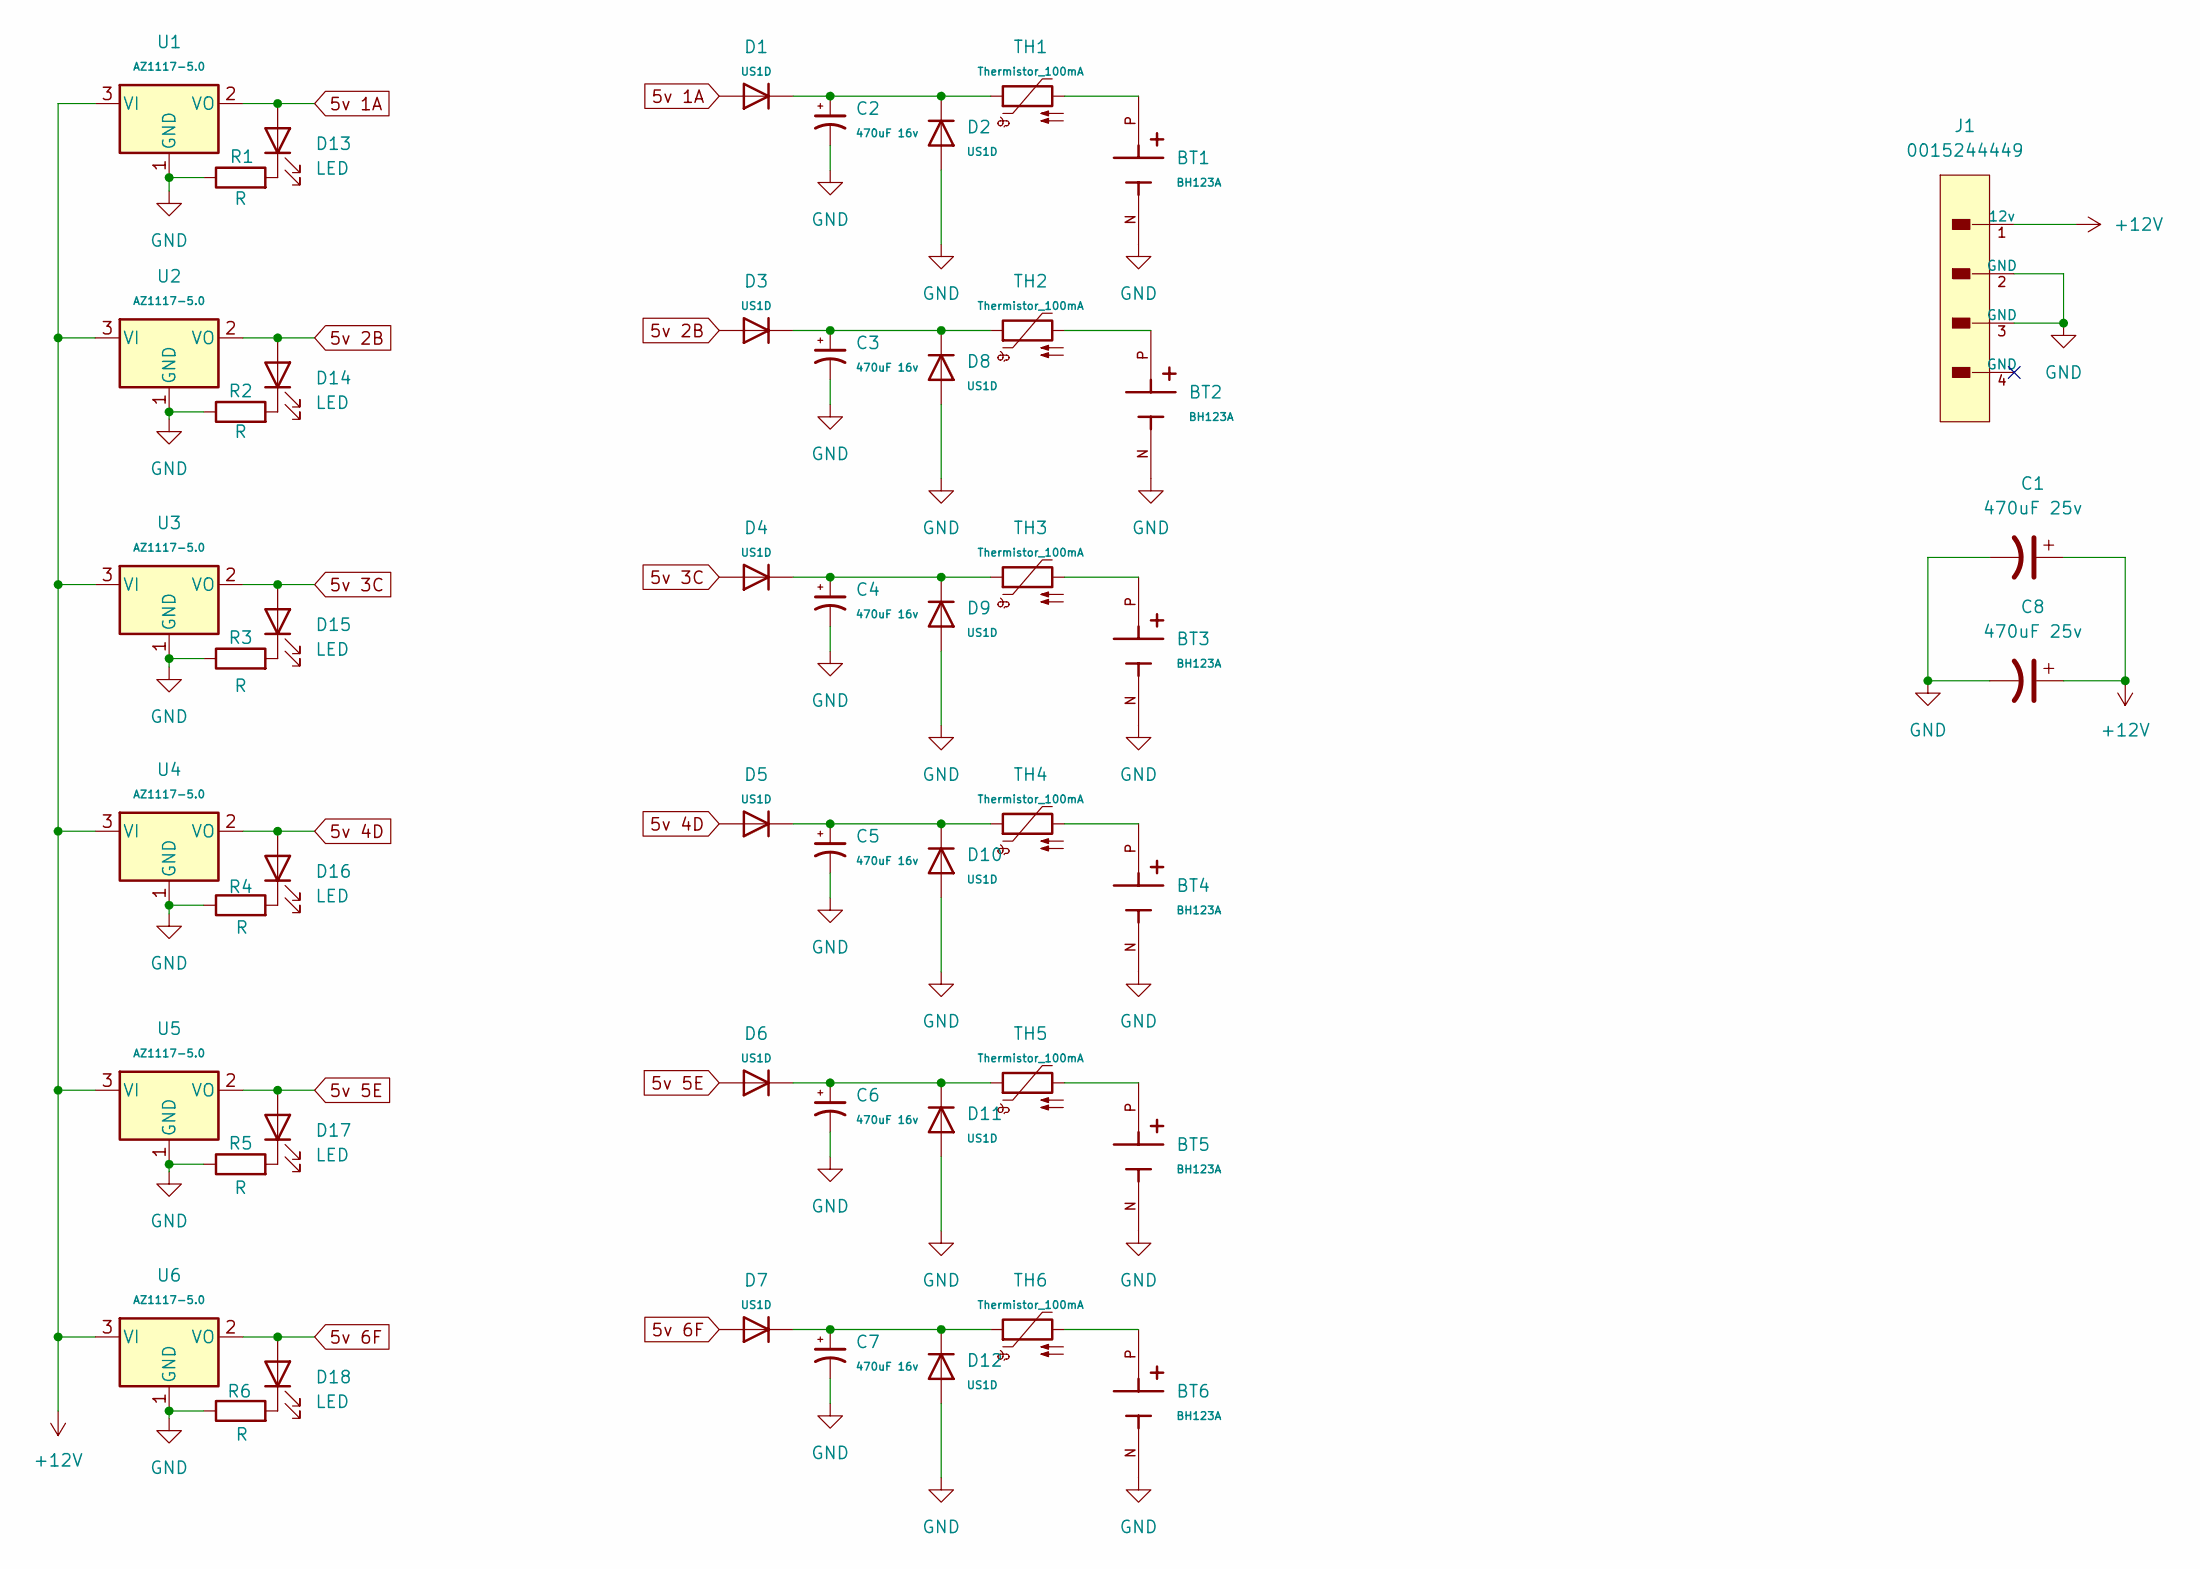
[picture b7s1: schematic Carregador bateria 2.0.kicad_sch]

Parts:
BT1, BT2, BT3, BT4, BT5, BT6: BH123A; BatteryHolder_cr123a
C1, C8: 470uF 25v; CP_Radial_D10.0mm_P5.00mm
C2, C3, C4, C5, C6, C7: 470uF 16v; CP_Radial_D8.0mm_P3.50mm
D1, D2, D3, D4, D5, D6, D7, D8, D9, D10, D11, D12: US1D; D_SMA
D13, D14, D15, D16, D17, D18: LED; LED_0603_1608Metric
J1: 0015244449; Molex_Mini-Fit_Jr_5569-20A2_2x10_P4.20mm_Horizontal; voltage 250VAC; mouser part number 538-15-24-4449; digikey description CONN HEADER 4POS .200 VERT
R1, R2, R3, R4, R5, R6: R; R_0603_1608Metric
TH1, TH2, TH3, TH4, TH5, TH6: Thermistor_100mA; R_1210_3225Metric
U1, U2, U3, U4, U5, U6: AZ1117-5.0; SOT-223-3_TabPin2

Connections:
5v 1A: D1.2 (A), D13.2 (A), U1.2 (VO)
5v 2B: D3.2 (A), D14.2 (A), U2.2 (VO)
5v 3C: D4.2 (A), D15.2 (A), U3.2 (VO)
5v 4D: D5.2 (A), D16.2 (A), U4.2 (VO)
5v 5E: D6.2 (A), D17.2 (A), U5.2 (VO)
5v 6F: D7.2 (A), D18.2 (A), U6.2 (VO)
+12V: C1.1, C8.1, J1.1 (12v), U1.3 (VI), U2.3 (VI), U3.3 (VI), U4.3 (VI), U5.3 (VI), U6.3 (VI)
GND: BT1.N, BT2.N, BT3.N, BT4.N, BT5.N, BT6.N, C1.2, C2.2, C3.2, C4.2, C5.2, C6.2, C7.2, C8.2, D2.2 (A), D8.2 (A), D9.2 (A), D10.2 (A), D11.2 (A), D12.2 (A), J1.2 (GND), J1.3 (GND), R1.1, R2.1, R3.1, R4.1, R5.1, R6.1, U1.1 (GND), U2.1 (GND), U3.1 (GND), U4.1 (GND), U5.1 (GND), U6.1 (GND)
unnamed: BT1.P, TH1.2
unnamed: BT2.P, TH2.2
unnamed: BT3.P, TH3.2
unnamed: BT4.P, TH4.2
unnamed: BT5.P, TH5.2
unnamed: BT6.P, TH6.2
unnamed: C2.1, D1.1 (K), D2.1 (K), TH1.1
unnamed: C3.1, D3.1 (K), D8.1 (K), TH2.1
unnamed: C4.1, D4.1 (K), D9.1 (K), TH3.1
unnamed: C5.1, D5.1 (K), D10.1 (K), TH4.1
unnamed: C6.1, D6.1 (K), D11.1 (K), TH5.1
unnamed: C7.1, D7.1 (K), D12.1 (K), TH6.1
unnamed: D13.1 (K), R1.2
unnamed: D14.1 (K), R2.2
unnamed: D15.1 (K), R3.2
unnamed: D16.1 (K), R4.2
unnamed: D17.1 (K), R5.2
unnamed: D18.1 (K), R6.2

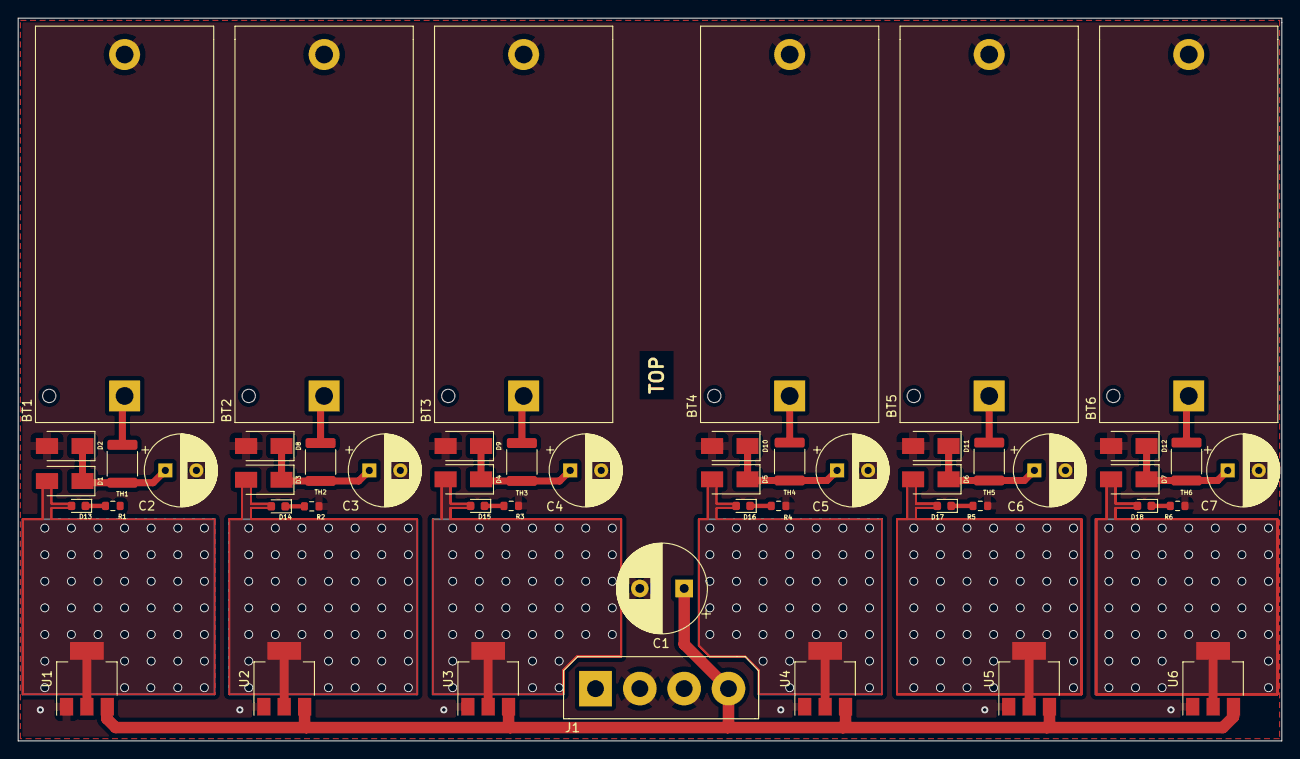
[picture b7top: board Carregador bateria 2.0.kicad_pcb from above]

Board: 2 copper layers, 142.5 x 81.5 mm, 50 parts (0 on the bottom side), 26 nets.
